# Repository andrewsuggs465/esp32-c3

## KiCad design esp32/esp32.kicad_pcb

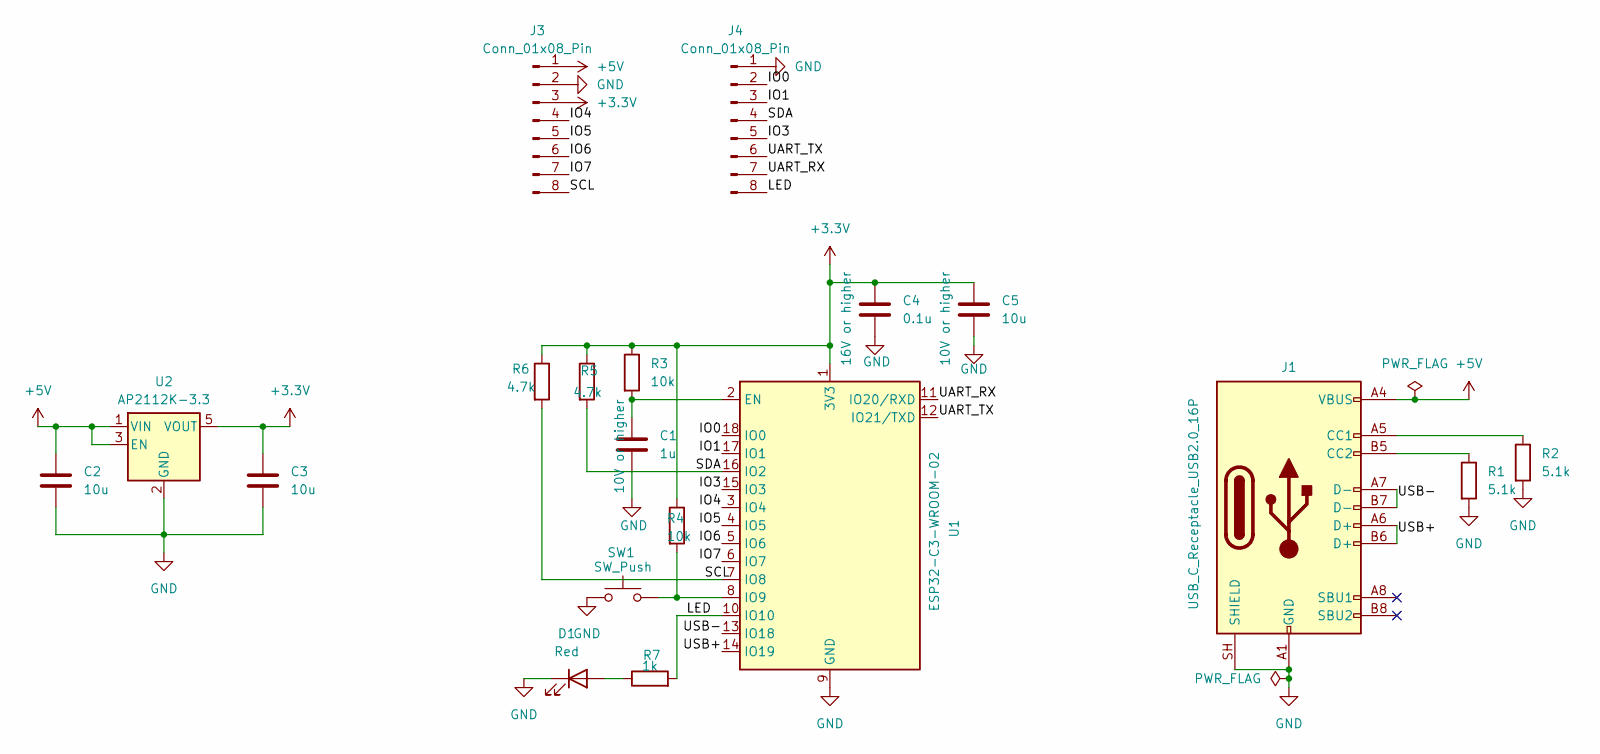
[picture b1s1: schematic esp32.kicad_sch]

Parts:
C1: 1u; C_0603_1608Metric
C2, C3, C5: 10u; C_0603_1608Metric
C4: 0.1u; C_0603_1608Metric
D1: Red; LED_0603_1608Metric
J1: USB_C_Receptacle_USB2.0_16P; USB_C_Receptacle_HRO_TYPE-C-31-M-12
J3, J4: Conn_01x08_Pin; PinHeader_1x08_P2.54mm_Vertical
R1, R2: 5.1k; R_0603_1608Metric
R3, R4: 10k; R_0603_1608Metric
R5, R6: 4.7k; R_0603_1608Metric
R7: 1k; R_0603_1608Metric
SW1: SW_Push; SW_SPST_PTS810
U1: ESP32-C3-WROOM-02
U2: AP2112K-3.3; SOT-23-5

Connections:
+3.3V: C3.1, C4.1, C5.1, J3.3, R3.1, R4.1, R5.1, R6.1, U1.1 (3V3), U2.5 (VOUT)
+5V: C2.1, J1.A4 (VBUS), J1.A9 (VBUS), J1.B4 (VBUS), J1.B9 (VBUS), J3.1, U2.1 (VIN), U2.3 (EN)
/IO0: J4.2, U1.18 (IO0)
/IO1: J4.3, U1.17 (IO1)
/IO3: J4.5, U1.15 (IO3)
/IO4: J3.4, U1.3 (IO4)
/IO5: J3.5, U1.4 (IO5)
/IO6: J3.6, U1.5 (IO6)
/IO7: J3.7, U1.6 (IO7)
/LED: J4.8, R7.2, U1.10 (IO10)
/SCL: J3.8, R6.2, U1.7 (IO8)
/SDA: J4.4, R5.2, U1.16 (IO2)
/UART_RX: J4.7, U1.11 (IO20/RXD)
/UART_TX: J4.6, U1.12 (IO21/TXD)
/USB+: J1.A6 (D+), J1.B6 (D+), U1.14 (IO19)
/USB-: J1.A7 (D-), J1.B7 (D-), U1.13 (IO18)
GND: C1.2, C2.2, C3.2, C4.2, C5.2, D1.1 (K), J1.A1 (GND), J1.A12 (GND), J1.B1 (GND), J1.B12 (GND), J1.SH (SHIELD), J3.2, J4.1, R1.2, R2.2, SW1.1, U1.9 (GND), U1.19 (GND), U2.2 (GND)
unnamed: D1.2 (A), R7.1
unnamed: J1.A5 (CC1), R2.1
unnamed: J1.B5 (CC2), R1.1
unnamed: C1.1, R3.2, U1.2 (EN)
unnamed: R4.2, SW1.2, U1.8 (IO9)

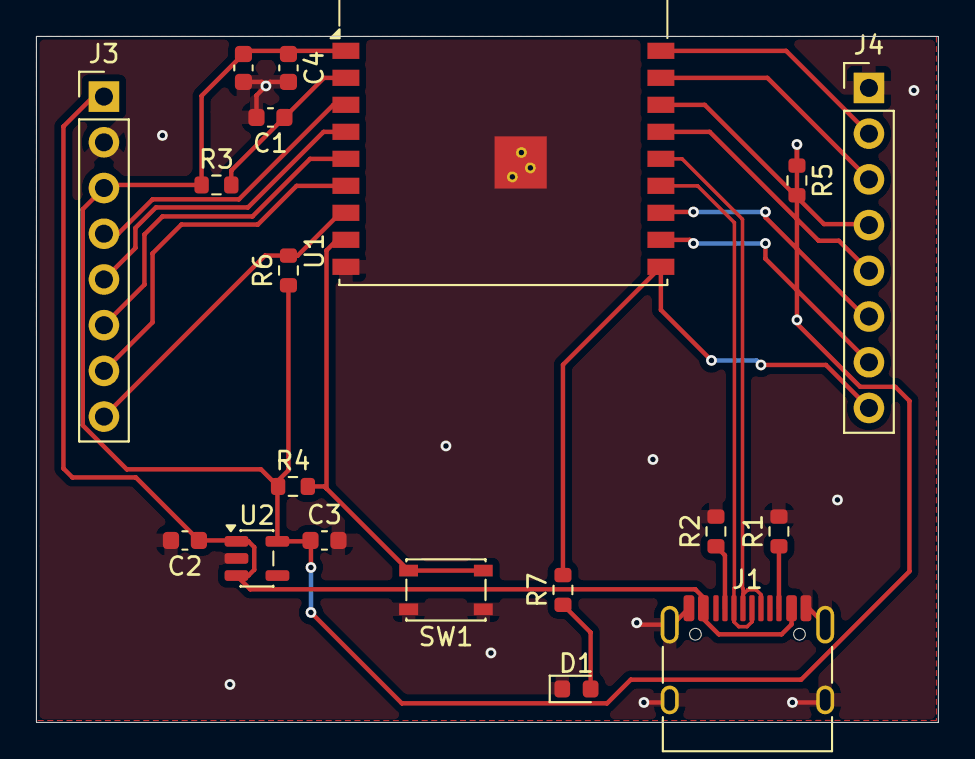
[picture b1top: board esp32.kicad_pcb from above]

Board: 2 copper layers, 50.1 x 38.1 mm, 19 parts (0 on the bottom side), 22 nets.
